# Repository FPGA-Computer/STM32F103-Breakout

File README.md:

This is a breakout board for the STM32F103 - TQFP48 Package

Eagle CAD/
Sketchup 3D Model/

Hackaday project page is at 
http://hw-by-design.blogspot.com/2018/08/stm32f103-breakout-board.html

Releases: 
forgot 1.5K pullup on USB D+,  fixed in v.3

This work is licensed under a Creative Commons Attribution-
NonCommercial-ShareAlike 4.0 International License.

The full detail of this license is available at: 
http://creativecommons.org/licenses/by-nc-sa/4.0/

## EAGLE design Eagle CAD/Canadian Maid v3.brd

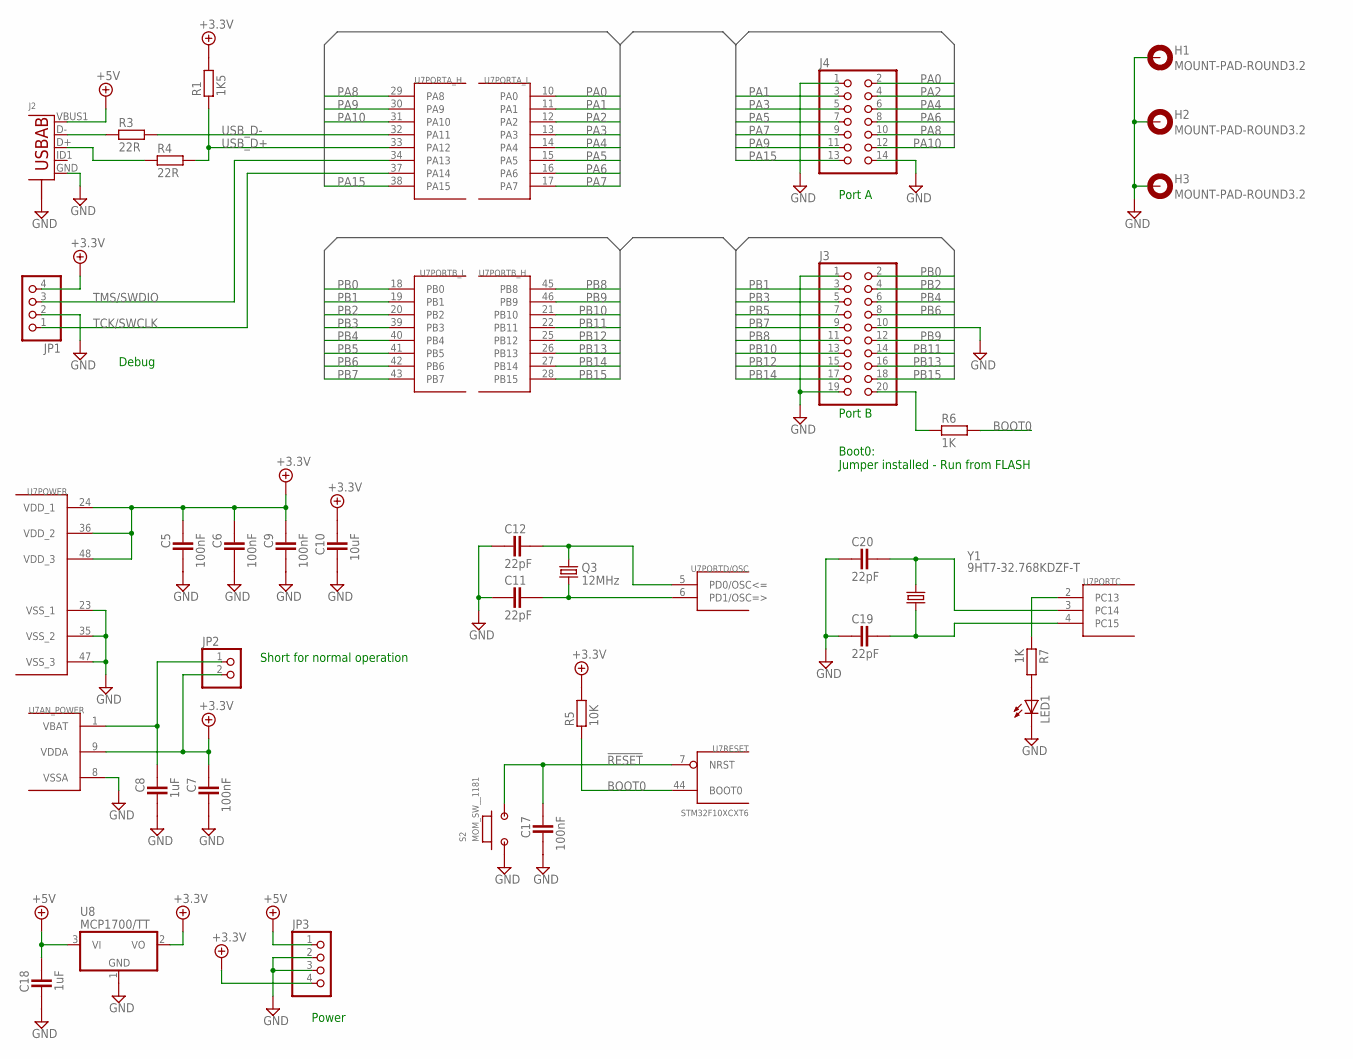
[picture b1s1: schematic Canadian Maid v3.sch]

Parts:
C5, C6, C7, C9, C17: 100nF; CAPC1005X60N
C8: 1uF; CAPC1005X60N
C10: 10uF; CAPC2012X145AN
C11, C12, C19, C20: 22pF; CAPC1005X60N
C18: 1uF; CAPC1608X92N
H1, H2, H3: MOUNT-PAD-ROUND3.2; 3,2-PAD
J2: USB-ABBG; USB-AB-MICRO-SMD_V03_SF
J3: PINHD-2X10_2.54; 2X10
J4: PINHD-2X7S; 2X07
JP1, JP3: PINHD-1X4_2.54; 1X04
JP2: PINHD-1X2_2.00; 1X02M
LED1: LEDSML0603; SML0603
Q3: 12MHz; HC49U-V
R1: 1K5; RESC1005X40AN
R3, R4: 22R; RESC1005X40AN
R5: 10K; RESC1005X40AN
R6, R7: 1K; RESC1005X40AN
S2: MOM_SW__1181; MOM-1181
U7: STM32F10XCXT6; TQFP48
U8: MCP1700/TT; SOT95P280X135-3N
Y1: 9HT7-32.768KDZF-T; 9HT7

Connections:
!RESET: C17.1, S2.2, U7.7 (NRST)
+3.3V: C5.1, C6.1, C7.1, C9.1, C10.1, JP1.4, JP2.2, JP3.4, R1.2, R5.2, U7.9 (VDDA), U7.24 (VDD_1), U7.36 (VDD_2), U7.48 (VDD_3), U8.2 (VO)
+5V: C18.1, J2.VBUS1 (VBUS), JP3.1, U8.3 (VI)
BOOT0: R5.1, R6.2, U7.44 (BOOT0)
GND: C5.2, C6.2, C7.2, C8.2, C9.2, C10.2, C11.1, C12.1, C17.2, C18.2, C19.1, C20.1, H1.B3,2, H2.B3,2, H3.B3,2, J2.GND, J2.S1 (S), J2.S2 (S), J2.S3 (S), J2.S4 (S), J3.1, J3.10, J3.19, J4.1, J4.14, JP1.2, JP3.2, JP3.3, LED1.C, S2.1, U7.8 (VSSA), U7.23 (VSS_1), U7.35 (VSS_2), U7.47 (VSS_3), U8.1 (GND)
unnamed: J2.D-, R3.1
unnamed: J2.D+, R4.1
unnamed: C8.1, JP2.1, U7.1 (VBAT)
unnamed: C12.2, Q3.2, U7.5 (PD0/OSC<=)
unnamed: C11.2, Q3.1, U7.6 (PD1/OSC=>)
unnamed: J3.20, R6.1
unnamed: C20.2, U7.3 (PC14), Y1.4 (2)
unnamed: C19.2, U7.4 (PC15), Y1.1
unnamed: R7.1, U7.2 (PC13)
unnamed: LED1.A, R7.2
PA0: J4.2, U7.10 (PA0)
PA1: J4.3, U7.11 (PA1)
PA2: J4.4, U7.12 (PA2)
PA3: J4.5, U7.13 (PA3)
PA4: J4.6, U7.14 (PA4)
PA5: J4.7, U7.15 (PA5)
PA6: J4.8, U7.16 (PA6)
PA7: J4.9, U7.17 (PA7)
PA8: J4.10, U7.29 (PA8)
PA9: J4.11, U7.30 (PA9)
PA10: J4.12, U7.31 (PA10)
PA15: J4.13, U7.38 (PA15)
PB0: J3.2, U7.18 (PB0)
PB1: J3.3, U7.19 (PB1)
PB2: J3.4, U7.20 (PB2)
PB3: J3.5, U7.39 (PB3)
PB4: J3.6, U7.40 (PB4)
PB5: J3.7, U7.41 (PB5)
PB6: J3.8, U7.42 (PB6)
PB7: J3.9, U7.43 (PB7)
PB8: J3.11, U7.45 (PB8)
PB9: J3.12, U7.46 (PB9)
PB10: J3.13, U7.21 (PB10)
PB11: J3.14, U7.22 (PB11)
PB12: J3.15, U7.25 (PB12)
PB13: J3.16, U7.26 (PB13)
PB14: J3.17, U7.27 (PB14)
PB15: J3.18, U7.28 (PB15)
TCK/SWCLK: JP1.1, U7.37 (PA14)
TMS/SWDIO: JP1.3, U7.34 (PA13)
USB_D+: R1.1, R4.2, U7.33 (PA12)
USB_D-: R3.2, U7.32 (PA11)

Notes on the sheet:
Short for normal operation
Power
Debug
Port A
Port B
Boot0: Jumper installed - Run from FLASH

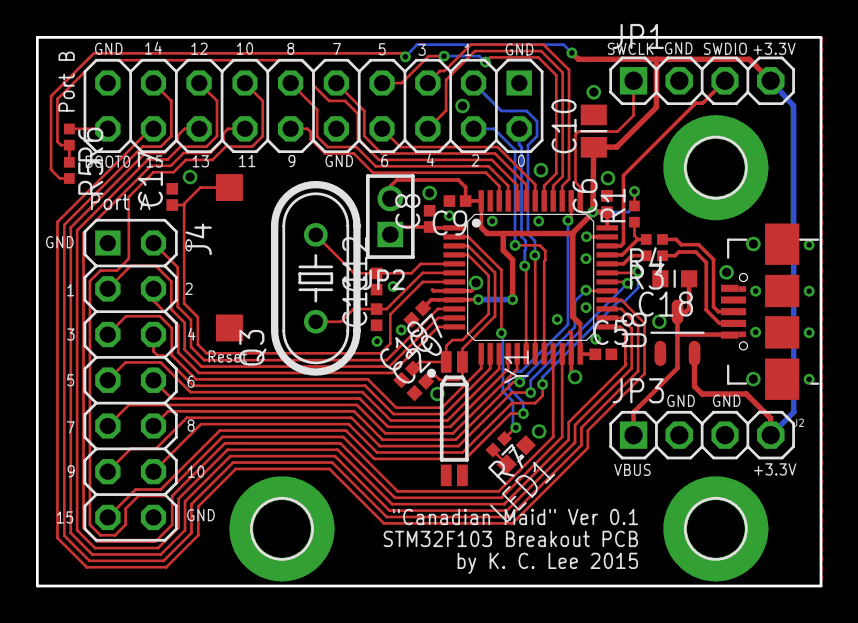
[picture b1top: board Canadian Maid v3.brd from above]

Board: 2 copper layers, 43.5 x 30.5 mm, 33 parts (0 on the bottom side), 47 nets.

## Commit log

2018-08-07 Update project hosting
2018-08-07 latest schematic/layout - fixed USB D+ pullup
